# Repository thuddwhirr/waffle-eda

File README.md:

# waffle-eda

Goal: An automated, claude code compatable tool suite who's purpose is to take an idea from feature proposal to manufacturable design files, with zero intervention from a human on routing or schematic layout. 

Desired Outcome:
 - Take user description of desired features and refine it into a design document (capabilities, size, port layout, etc)
 - Take design document and build out a BOM (bill of materials), constrained by user's cost limits and manufacturer choice
 - Take parts list and build out a schematic (hopefully one a human EE could read and review)
 - Take design document, parts list and manufacturer choice and determine PCB charecteristcs (dimensions, layers, materials, via types, etc)
 - Place and Route loop: taking PCB specifications, schematic, and BOM: 
    - do a parts layout on the board. 
    - route traces
    - apply electric and design rule checks
    - revise as needed until completion, or fail with report of needed changes. 
 - Take completed PCB and BOM to create manufacturing files for upload to vendor.

## Definition

"Zero intervention" means zero interactive routing. The owner reviews outputs and decides design revisions; the tool
never hands back a list of nets to finish by hand. A routing run ends complete or fails with a diagnosis. The tool
may change placement, pin assignment, layer count, via type and board size on its own; it asks the owner only about
the maximum board size, material cost, and agreed interface positions. The full definition, the pipeline's six stages
and their gates, and the working agreement are in [`docs/definition.md`](docs/definition.md).

## Plan

One class of board at a time, the whole pipeline for that class before the next class is touched: class A (two
layers, a microcontroller, passives), then B (four layers, a USB pair, a switcher, planes), then B+ (a BGA with
no matched bus), then C (a BGA FPGA with DDR3). Each class is gated on every open-hardware reference board in
it and on one synthetic design taken to fab outputs. The interface is Claude Code, files, renders and reports; a
user interface is a separate project. See [`docs/plan.md`](docs/plan.md).

## Layout

| Path | What |
|---|---|
| [`docs/plan.md`](docs/plan.md) | the ladder, the milestones, what exists, and what the next session does |
| [`docs/definition.md`](docs/definition.md) | the project definition: stages, gates, acceptance rule, free variables and locked constraints |
| [`docs/decisions.md`](docs/decisions.md) | the decisions log: what the owner decided and what was measured |
| [`docs/references.md`](docs/references.md) | the reference boards, measured |
| [`docs/lessons/`](docs/lessons/README.md) | documents carried from `waffle-fpga`, with provenance |
| [`docs/research/`](docs/research/) | the DDR3 routing research; read when class C starts |
| [`docs/archive/`](docs/archive/README.md) | the first five days' plan, router spec and full log; not read at session start |
| `waffle_eda/` | the package: `kicad/` board helpers, `bench/` reference boards and scoring, `fab/` vendor profiles, `route/` routers |
| `scripts/` | entry points: environment check, tool and reference fetch, measurements, the gates, `design.py` (a design through the six stages, and its status) |
| `designs/` | design directories: `design.md`, `bom.csv`, `kicad/`, `netlist.net`, `spec.toml`, `reports/`, `out/` (the class A synthetic design, `temperature-sensor`) |
| `tests/` | unit tests; tests that need the reference boards or the fetched libraries skip when they are absent |
| [`salvage/waffle-fpga/`](salvage/waffle-fpga/README.md) | the previous project's tools, verbatim, for reference only |
| `references/` | the fetched reference boards (ignored by git; see the fetch script for licences) |
| `build/` | generated outputs (ignored by git) |

## Quick start

Needs KiCad 9 with its Python bindings on the interpreter that runs these scripts (`python3 -c "import pcbnew"`).

```sh
pip install -e ".[dev]"                     # z3-solver, numpy, shapely, pytest
python3 scripts/fetch_tools.py              # Freerouting, a Java 25, KiCad's symbol and footprint libraries, into build/tools/
python3 scripts/check_env.py                # KiCad 9, pcbnew, z3, Java, Xvfb, the libraries
python3 scripts/fetch_references.py         # clones the reference boards into references/
python3 scripts/gate.py a                   # the class A gate: strip each reference to placement, re-route, score
python3 scripts/design.py run temperature-sensor     # the class A synthetic design through the six stages to out/
python3 scripts/design.py status temperature-sensor  # each gate's state and what waits on the owner
python3 scripts/gate.py escape              # the BGA escape gate (class B+)
python3 scripts/gate.py busplan             # the bus plan gate (class C)
python3 scripts/rebuild_bench.py tinkerforge-temperature   # one board of the class A benchmark, with its files kept
python3 scripts/measure_references.py       # writes build/measure-<board>.json and prints a summary
python3 -m pytest -q -rs
```

## Status

2026-09-24. **Class A: both halves run green; the owner's review is what remains.** The class A gate passes on
all five references (every net routed, zero violations under each board's measured rules, 13 s to 7 min a
board) with Freerouting 2.4.1 inside the wrapper's repairs as stage 5's baseline. The synthetic
temperature-sensor design is through all six stages to fab outputs (`designs/temperature-sensor/out/`), every
gate PASS; it waits on the owner's review of its design document and outputs, and on prices, which are unknown
and escalated. The BGA escape gate (9 of 9 cases) and the bus plan gate (3 of 3 class C references) pass and
wait for classes B+ and C. The DDR3 bus routing is parked at 42 of 55 nets on ButterStick until then.

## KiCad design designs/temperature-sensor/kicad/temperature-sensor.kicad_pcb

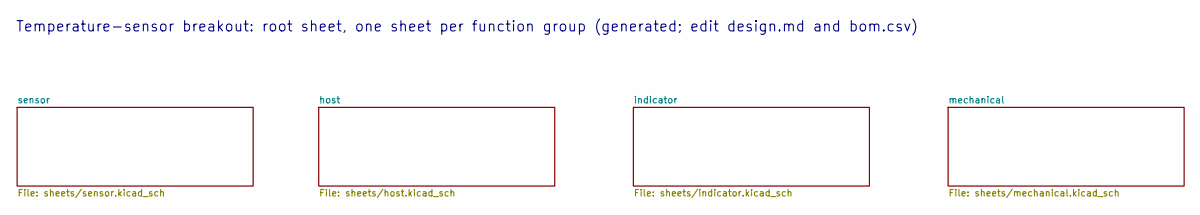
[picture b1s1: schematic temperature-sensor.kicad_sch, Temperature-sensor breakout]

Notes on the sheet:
Temperature-sensor breakout: root sheet, one sheet per function group (generated; edit design.md and bom.csv)

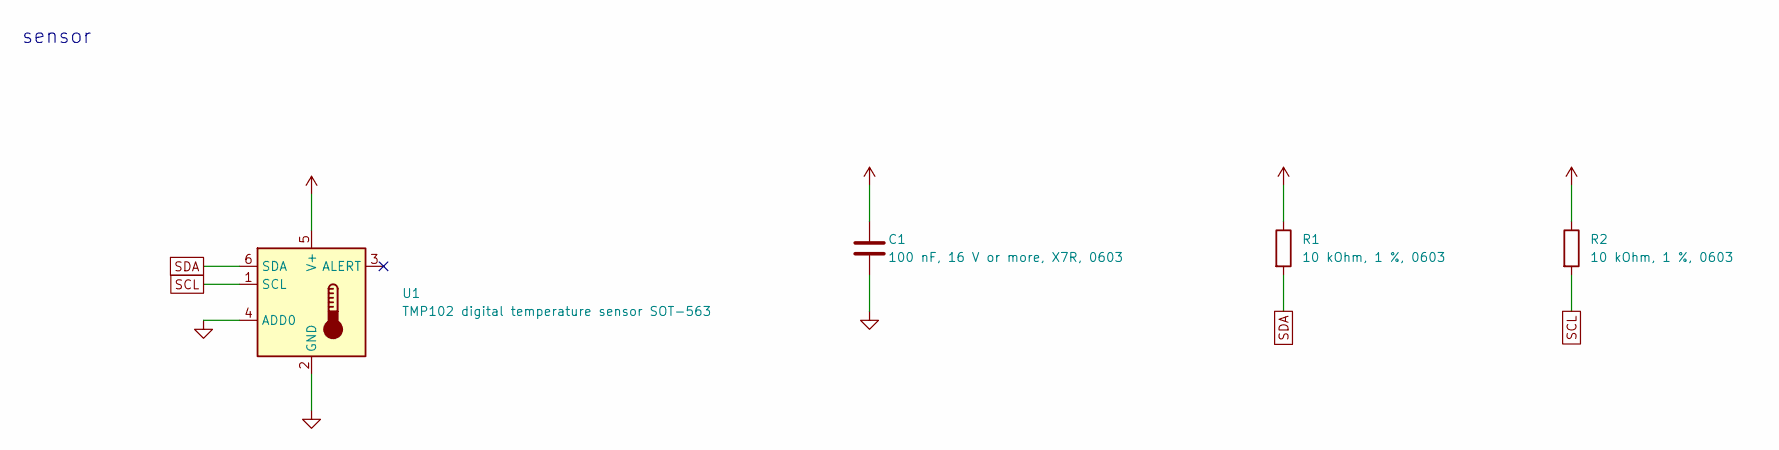
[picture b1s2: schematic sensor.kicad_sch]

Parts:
C1: 100 nF, 16 V or more, X7R, 0603; C_0603_1608Metric; MPN any
R1, R2: 10 kOhm, 1 %, 0603; R_0603_1608Metric; MPN any
U1: TMP102 digital temperature sensor SOT-563; SOT-563; MPN TMP102AIDRLR (from the symbol's part na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

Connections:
GND: C1.2, U1.2 (GND), U1.4 (ADD0); also elsewhere on the board
SCL: R2.2, U1.1 (SCL); also elsewhere on the board
SDA: R1.2, U1.6 (SDA); also elsewhere on the board
VCC: C1.1, R1.1, R2.1, U1.5 (V+); also elsewhere on the board

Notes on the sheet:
sensor

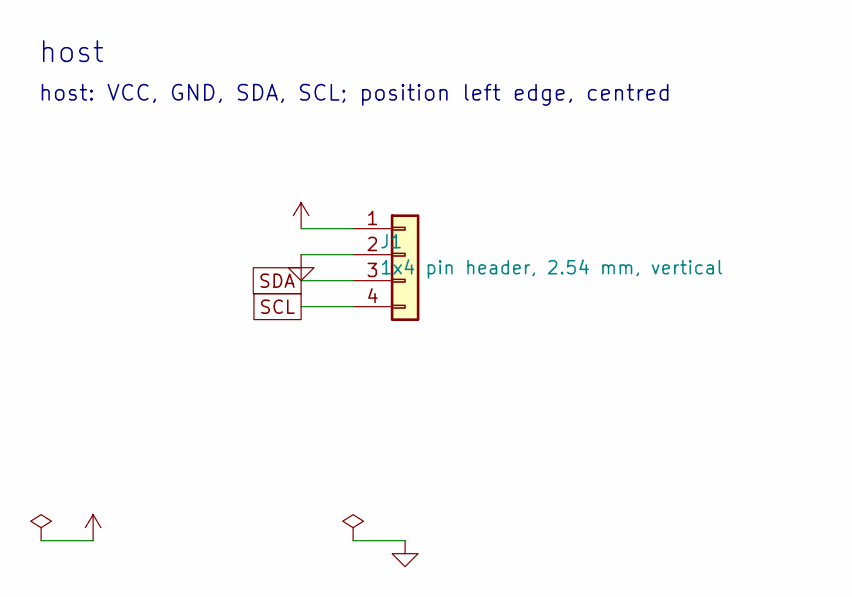
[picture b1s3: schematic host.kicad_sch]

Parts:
J1: 1x4 pin header, 2.54 mm, vertical; PinHeader_1x04_P2.54mm_Vertical; MPN any

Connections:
GND: J1.2; also elsewhere on the board
SCL: J1.4; also elsewhere on the board
SDA: J1.3; also elsewhere on the board
VCC: J1.1; also elsewhere on the board

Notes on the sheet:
host
host: VCC, GND, SDA, SCL; position left edge, centred

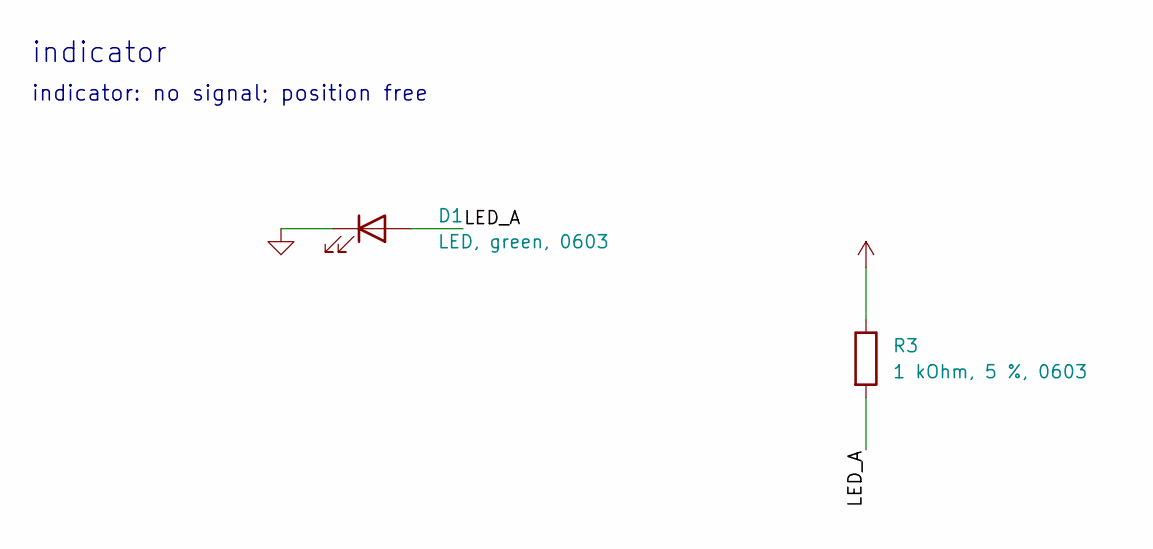
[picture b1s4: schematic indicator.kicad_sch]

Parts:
D1: LED, green, 0603; LED_0603_1608Metric; MPN any
R3: 1 kOhm, 5 %, 0603; R_0603_1608Metric; MPN any

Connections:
/indicator/LED_A: D1.2 (A), R3.2
GND: D1.1 (K); also elsewhere on the board
VCC: R3.1; also elsewhere on the board

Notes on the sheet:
indicator
indicator: no signal; position free

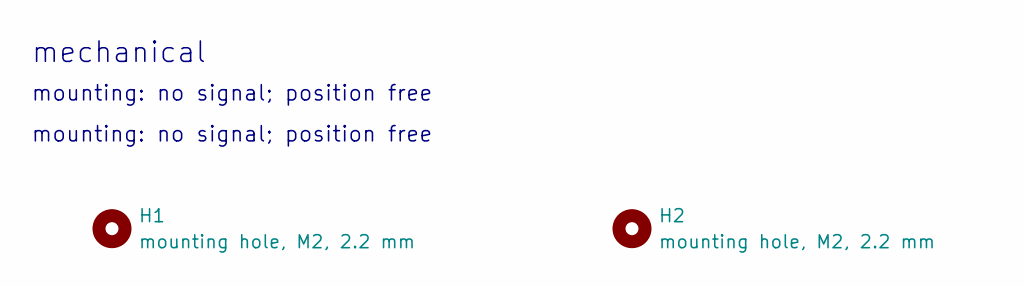
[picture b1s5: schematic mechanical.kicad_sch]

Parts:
H1, H2: mounting hole, M2, 2.2 mm; MountingHole_2.2mm_M2; MPN none

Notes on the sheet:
mechanical
mounting: no signal; position free

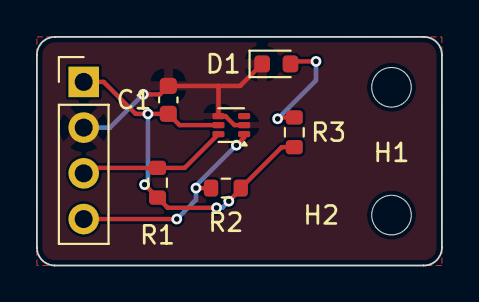
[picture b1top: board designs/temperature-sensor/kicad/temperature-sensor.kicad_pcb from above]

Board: 2 copper layers, 22.5 x 12.7 mm, 9 parts (0 on the bottom side), 5 nets.

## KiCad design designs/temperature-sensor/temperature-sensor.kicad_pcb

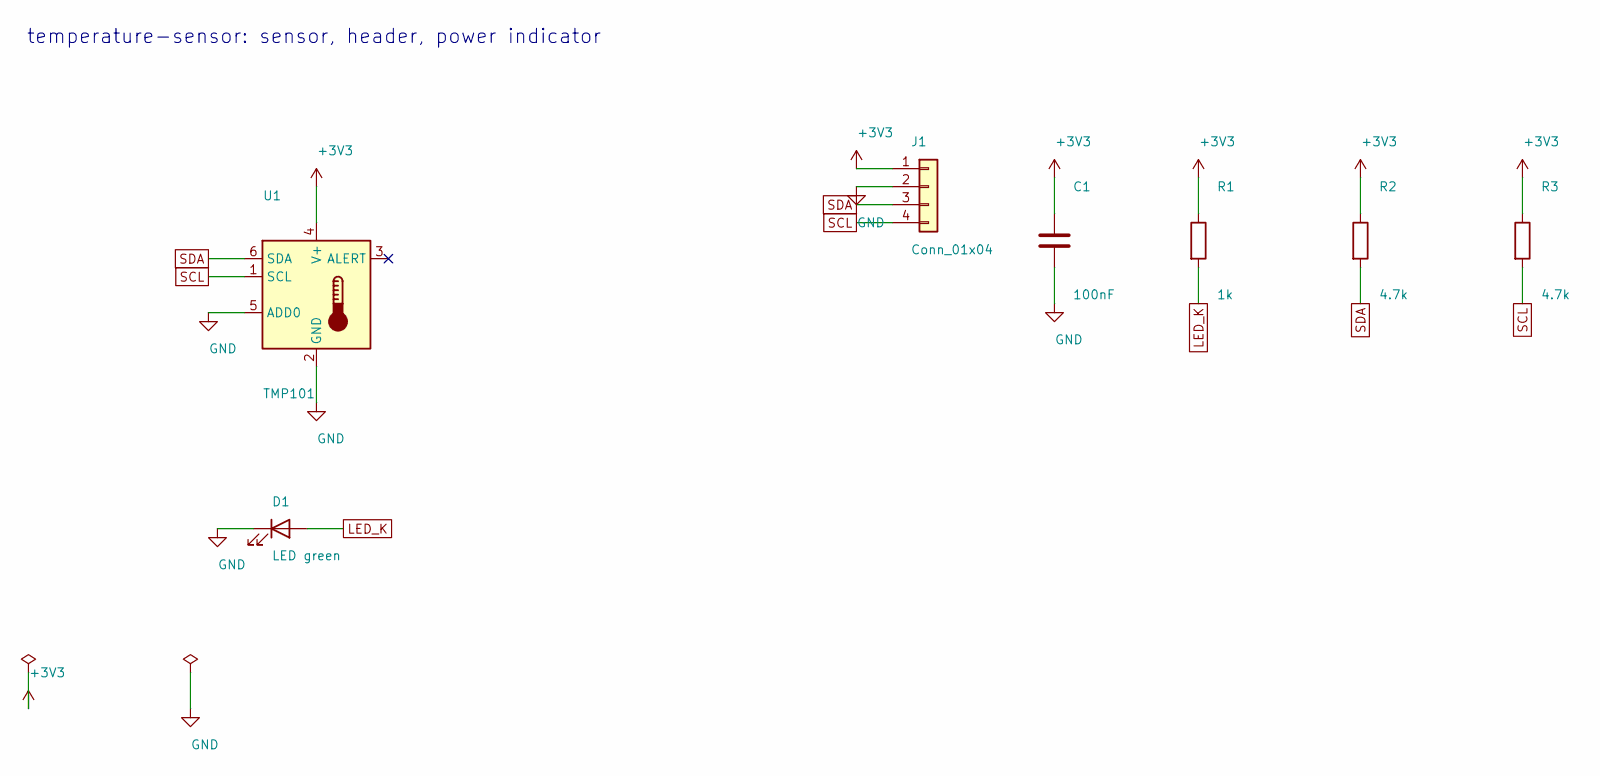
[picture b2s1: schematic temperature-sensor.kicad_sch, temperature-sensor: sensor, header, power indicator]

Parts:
C1: 100nF; C_0603_1608Metric
D1: LED green; LED_0603_1608Metric
J1: Conn_01x04; PinHeader_1x04_P2.54mm_Vertical
R1: 1k; R_0603_1608Metric
R2, R3: 4.7k; R_0603_1608Metric
U1: TMP101; SOT-23-6

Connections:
+3V3: C1.1, J1.1, R1.1, R2.1, R3.1, U1.4 (V+)
GND: C1.2, D1.1 (K), J1.2, U1.2 (GND), U1.5 (ADD0)
LED_K: D1.2 (A), R1.2
SCL: J1.4, R3.2, U1.1 (SCL)
SDA: J1.3, R2.2, U1.6 (SDA)

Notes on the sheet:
temperature-sensor: sensor, header, power indicator

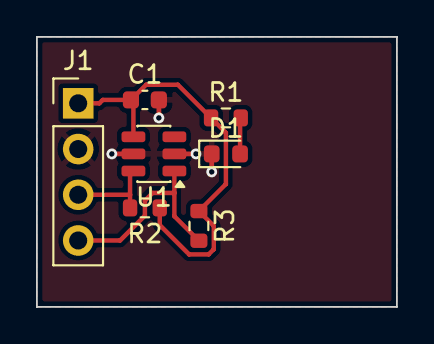
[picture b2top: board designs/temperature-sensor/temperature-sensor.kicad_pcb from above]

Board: 2 copper layers, 20.0 x 15.0 mm, 7 parts (0 on the bottom side), 5 nets.
